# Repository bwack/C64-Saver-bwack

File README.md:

C64 Saver v1 and v2
- Overvoltage protection for the C64 and its power brick.

Designed by BWACK 2018
CERN OPEN HARDWARE LICENSE v1.2
http://www.ohwr.org/

The KiCad and other design files are available on GitHub:
https://github.com/bwack/

All text above must be included in any redistribution

# Warning: latest version of the savers are not tested.

# Bwack's C64 saver designs.

The C64 Saver 2 is an open-source project intended to make overvoltage protection available and easy to make for anyone interested in using the old Commodore power brick together with the C64. The power brick is 30-40 years old, and it is known for failure with overvoltage. This is caused sometimes because of broken solder joints on the regulator or the regulator itself failing.

## What has changed in v2 ?
- The design is modular.
- Spike protection. Handles hotswapping and switch bouncing better.
- It is much much easier and faster to make. Most people can make it!

## The base board (C64 Saver 2 SMD or Throughhole)
The base board is all you need for overvoltage protection. Through hole parts except for the mosfet, but it is large and easy to solder, no special tools needed other than your solder iron. The board shape fits the Hammond 1551g project case.
* Note: You need to bridge pin 4 and 5 in J2 and pin 4 and 5 in J4 if you are not using the base board in combination with the addon board or the relay board. The reason for this is that, with the addon board, we need to route the current through a sensing circuit. When the addon board is not used, we need to route it directly to the mosfet and terminals.

There is also a SMD version for those who like to reflow soldering.

## The addon board
The C64 saver addon board is a hat for the base board, and adds software control, instrumentation on both ac and dc side, and an optional 128x32 OLED display. The aim for this project is to make a tool for C64 repairers. The 9VAC and 5VDC are fully isolated. Software control and instrumentation is useful if you are repairing C64s. You can set the output to shut down in case of an overcurrent condition. If an overvoltage happens you can configure the saver to auto reset or keep the power from comming back on again. There are several reasons why you might want this. C64 PSUs that need service, the capacitors are dry and the 5VDC has an AC component on it. The saver would normally just go on and off at 100Hz. The software control can detect this. The other problem is if the computer has a faulty chip that cause massive current draw on the 5V. The fuse might not blow because it is not enough, then you can configure the saver cut if you desire. I'm not gonna lie. This is my pet project, and the cost has not been a topic on my mind.

The C64 Saver Addon Board 1.4:

Youtube video of me testing the addon board installed on the C64 Saver 2.

The relay and hold board is archived in the oldfiles folder.

## C64 Saver OCP

OCP, not robocop, but overcurrent protection. Is a new circuit that I'm working on. It has three LEDs and a button. The overvoltage protection circuit is the same as before. The overcurrent will light the yellow led and keep it lit and keep the output OFF after an overcurrent event.

## The old design
I have decided to release my older C64 Saver v1. The board that fits inside a connector. Time and skill is super high on this product so be warned ! (SMD 0603, solder blob connections, tight spaces and short circuit hazards).

## Gerbers
If you are looking for gerbers, click the releases tab. There you will find a zip file of gerber for each release.

# BOM
All bill of materials (BOM) are moved into the respective project folders. I have added digikey etc order no. in the parts in the schematics such that they will show up in the interactive boms.

Here are the interactive BOMs:

[ibom for C64 Saver Throughole 2.6](https://htmlpreview.github.io/?https://github.com/bwack/C64-Saver-bwack/blob/master/C64%20Saver%20Throughhole%202.6/bom/ibom.html)

[ibom for C64 Saver SMD 2.6](https://htmlpreview.github.io/?https://github.com/bwack/C64-Saver-bwack/blob/master/C64%20Saver%20SMD%202.6/bom/ibom.html)

[ibom for C64 Addon Board 1.4](https://htmlpreview.github.io/?https://github.com/bwack/C64-Saver-bwack/blob/master/addon%20board%201.4/bom/ibom.html)

[ibom for C64 Saver OCP 0.1](https://htmlpreview.github.io/?https://github.com/bwack/C64-Saver-bwack/blob/master/C64%20Saver%20OCP%200.1/bom/ibom.html)

# Changelog:

- C64 Saver 2.6 (THT+SMD) and Addon Board 1.4 (2023-04-02)
  - Replaced 7n2002 with BC547/BC847 to fix the tolerance issues.
  - Throughhole and SMD: same version numbers, same circuits, same reference numbers.
  - Red LED is switched by TL431 and Green by BC547/BC847.
  - Added LEDs to the Throughhole version. It was a challenge.
  - Fix: The Addon Board 1.3 had incorrect pinout for the 5V reg.
  - I never tested the Addon Board 1.3, but thanks to Retroisten who sent.
  me images and advicing me about he pinout, I'm very happy about it. He also
  showed me that it does work, with the regulator hacked in.  In this version 1.4
  it is working.

- C64 Saver 2.5 (SMD) (2020-09-13)
  - Added fault LED and power LED
  - 0805 SMD resistors
  - SOT23-5 TL431 and NMOS

- RelayHold 0.2 (2019-08-25)
  - Initial release
  - All through-hole parts.

- Addon Board 1.3 (2019-05-24)
  - Changed optocoupler footprint to more common SOIC-4_4.55x2.6mm_P1.27mm
  - Larger 5V regulator on 9vac side for less heat
  - replaced 100uF tantalum with 3x 47uF 1206 MLCC
  - kicad 5.1.0 project

- Addon Board 1.2 (2018-11-11)
  - Swapped HOLD_ with SENSE_VAC on the MCU. SENSE_VAC needs ADC.
  - Correct the mixed up SDA and SCL.
  - 5V supply to the 5V section is moved to VIN+ (before the shunt).
    To not pull power through the sensing resistor.
  - 4k7 I2C pullups.https://htmlpreview.github.io/?https://github.com/bwack/C64-Saver-bwack/blob/develop/C64%20Saver%20Throughhole%202.6/bom/ibom.html

- C64 Saver 2.4 (2018-09-23)
  - Support lower Vth on Q1. Resistor divider R7 and R8.
  - Remove C2 to make room for resistor divider.
  - Changed R5 to 3k3 to reduce BOM size.
  - New layout and routing.

- Addon Board 1.1 (2018-09-23)
  - ATtiny85 is a 8S2 package and two mm wider than SOIC8.
  - Read overvoltage signal on reset pin using ADC. Added voltage divider.
  - Replace MCP1700 with MCP1703. Supporting higher Vin_max

- C64 Saver 2.3 (2018-08-18)
  - Q1 2N7002 pin 1 and 2 rotated
  - Q2 Reversed drain and source
  - Increased pullup on Q1 drain.
  - Repurposed R5 as pullup for Q1 drain.
  - tested bodged v2.2 prototype, wohttps://htmlpreview.github.io/?https://github.com/bwack/C64-Saver-bwack/blob/develop/C64%20Saver%20Throughhole%202.6/bom/ibom.htmlrking!

- C64 Saver 2.2 (2018-08-16)
  - R1 was rotated.

- C64 Saver 2.1 & Addon 1.0 (2018-07-23)
  - 5x 9VAC pins. 9VAC1 current (4x) + 9VAC2.
  - Moved GND pin.
  - Changed board size to fit Hammond1551g
  - C64 Saver board:
    - Smaller throughole resistors
    - Moved C1 closer to input circuits.
  - Addon board:
    - VAC sense circuit with voltage divider.
    - 5V regulator on VCC pin. RAW pin disconnected.
    - Pullups on I2C busses.
    - SSOP-4 optocoupler packages
    - Another regulator on the 5V side to protect the iso1541 and ina219.

- C64 Saver 2.0beta & Addon 1.0beta (2018-07-02)
  - New design.
  - Protected sensitive parts.
  - baseboard: throughhole parts.
  - C64 saver 2 addon board.
  - problem: has conflicting pinouts.

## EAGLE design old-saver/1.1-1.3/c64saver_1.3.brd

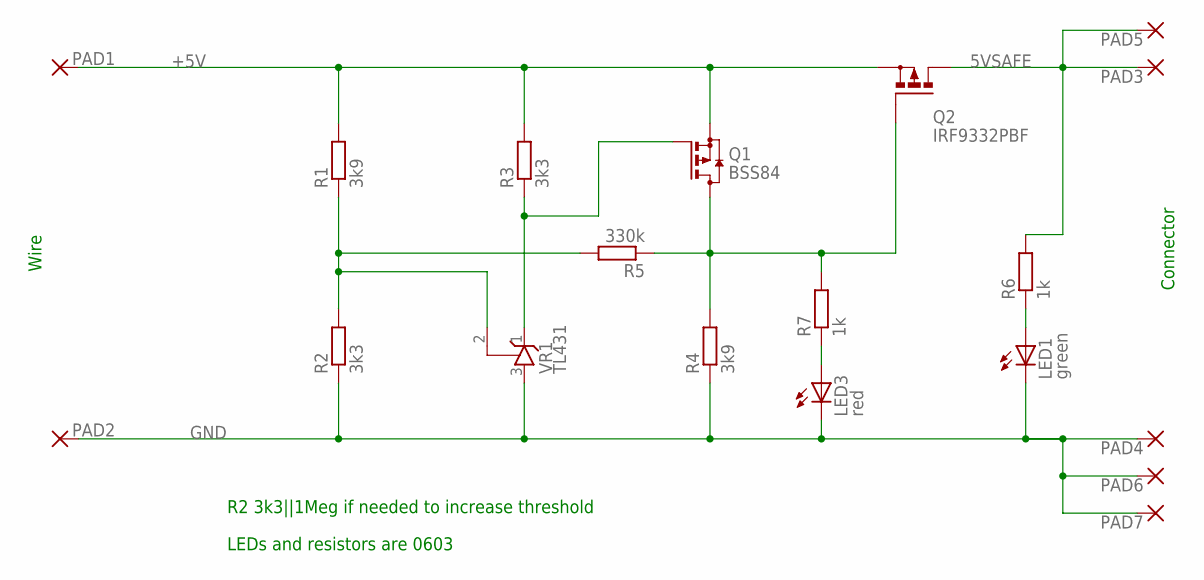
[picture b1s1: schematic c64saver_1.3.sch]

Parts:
LED1: green; CHIPLED_0603
LED3: red; CHIPLED_0603
PAD1, PAD2, PAD4, PAD6, PAD7: WIREPADSMD1,27-254; SMD1,27-2,54
PAD3, PAD5: WIREPADSMD2,54-2,54; SMD2,54-2,54
Q1: BSS84; SOT23
Q2: IRF9332PBF; SO-08
R1, R4: 3k9; R0603
R2, R3: 3k3; R0603
R5: 330k; R0603
R6, R7: 1k; R0603
VR1: TL431; SOT23

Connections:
5VSAFE: PAD3.1, PAD5.1, Q2.5 (D), Q2.6 (D), Q2.7 (D), Q2.8 (D), R6.2
+5V: PAD1.1, Q1.2 (S), Q2.1 (S), Q2.2 (S), Q2.3 (S), R1.2, R3.2
GND: LED1.C, LED3.C, PAD2.1, PAD4.1, PAD6.1, PAD7.1, R2.1, R4.1, VR1.3 (A)
unnamed: LED3.A, R7.1
unnamed: R1.1, R2.2, R5.2, VR1.2 (R)
unnamed: LED1.A, R6.1
unnamed: Q1.1 (G), R3.1, VR1.1 (C)
unnamed: Q1.3 (D), Q2.4 (G), R4.2, R5.1, R7.2

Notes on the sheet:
R2 3k3||1Meg if needed to increase threshold
Wire
Connector
LEDs and resistors are 0603

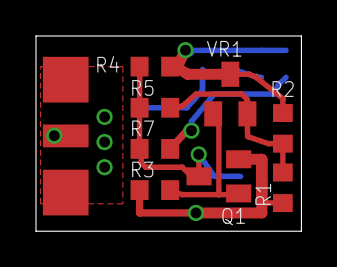
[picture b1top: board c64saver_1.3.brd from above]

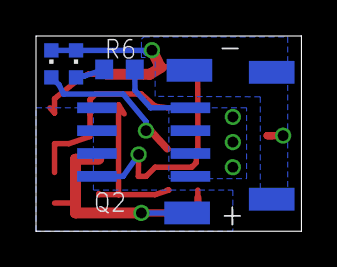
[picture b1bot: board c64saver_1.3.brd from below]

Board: 2 copper layers, 14.7 x 10.8 mm, 19 parts (8 on the bottom side), 8 nets.

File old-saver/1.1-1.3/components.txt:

The fet: IRF9333PBF (on sale)

Kontrollkabel uskjermet 4 x0.56 mm² uskjermet, UL-LIYY 4XAWG20, 2464/1061
10-416-96 19.90 pr meter

1   1k           R-EU_R0603         R7                                      
2   3k3          R-EU_R0603         R2, R3                                  
2   3k9          R-EU_R0603         R1, R4                                  
1   100k         R-EU_R0603         R5                                      
1   BSS84        BSS84              Q1                                      
1   IRF9332PBF   P-MOSFET-SO8       Q2                                      
1   RED_SIDEView LEDCHIPLED_1206    LED1                                    
1   TL431        TL431CLPSOT23      VR1

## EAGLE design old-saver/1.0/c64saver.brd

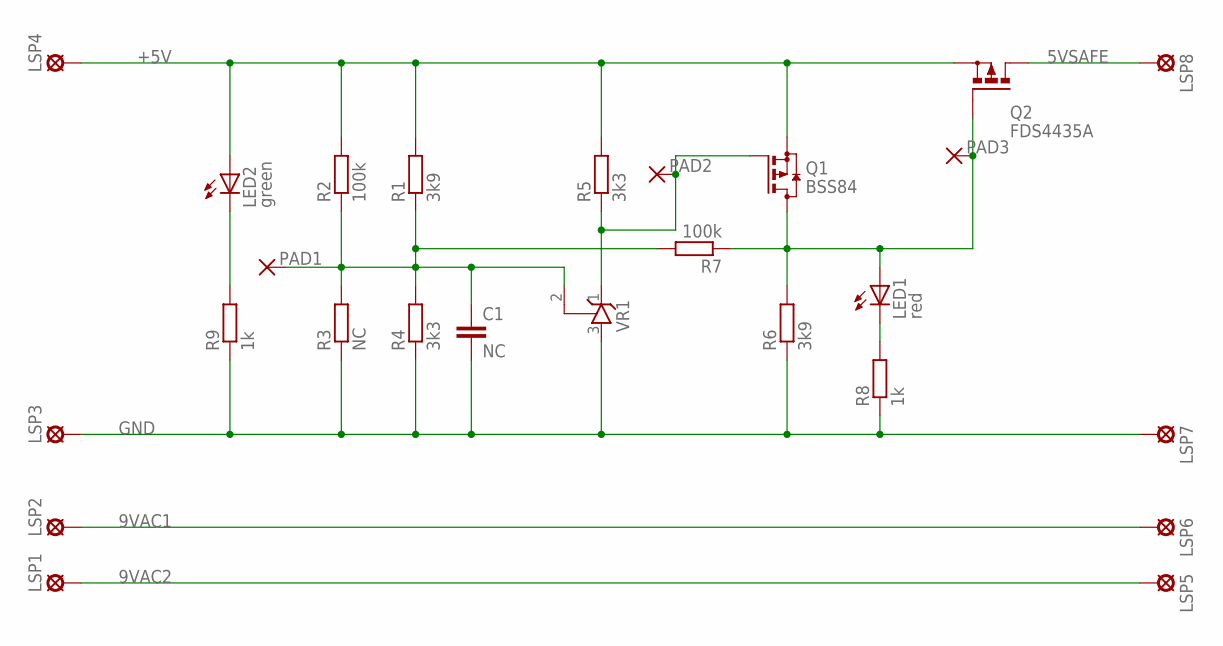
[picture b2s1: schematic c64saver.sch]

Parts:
C1: NC; C0603
LED1: red; CHIPLED_1206
LED2: green; CHIPLED_1206
LSP1, LSP2, LSP3, LSP4, LSP5, LSP6, LSP7, LSP8: SE14
PAD1, PAD2, PAD3: SMD2; SMD1,27-2,54
Q1: BSS84; SOT23
Q2: FDS4435A; SO-08
R1, R6: 3k9; R0603
R2, R7: 100k; R0603
R3: NC; R0603
R4, R5: 3k3; R0603
R8, R9: 1k; R0603
VR1: TL431CLPSOT23; SOT23

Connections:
5VSAFE: LSP8.MP, Q2.5 (D), Q2.6 (D), Q2.7 (D), Q2.8 (D)
9VAC1: LSP2.MP, LSP6.MP
9VAC2: LSP1.MP, LSP5.MP
+5V: LED2.A, LSP4.MP, Q1.2 (S), Q2.1 (S), Q2.2 (S), Q2.3 (S), R1.2, R2.2, R5.2
GND: C1.2, LSP3.MP, LSP7.MP, R3.1, R4.1, R6.1, R8.1, R9.1, VR1.3 (A)
unnamed: C1.1, PAD1.1, R1.1, R2.1, R3.2, R4.2, R7.2, VR1.2 (R)
unnamed: LED1.C, R8.2
unnamed: LED2.C, R9.2
unnamed: PAD2.1, Q1.1 (G), R5.1, VR1.1 (C)
unnamed: LED1.A, PAD3.1, Q1.3 (D), Q2.4 (G), R6.2, R7.1

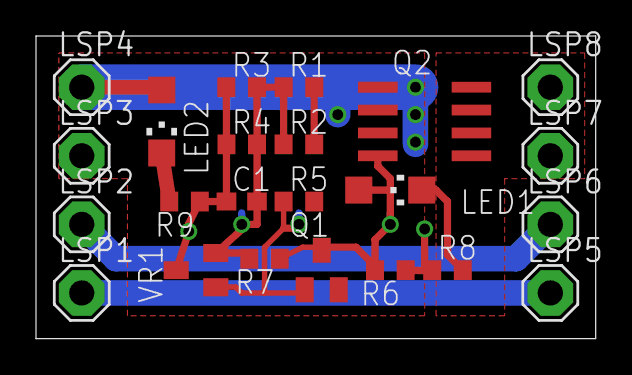
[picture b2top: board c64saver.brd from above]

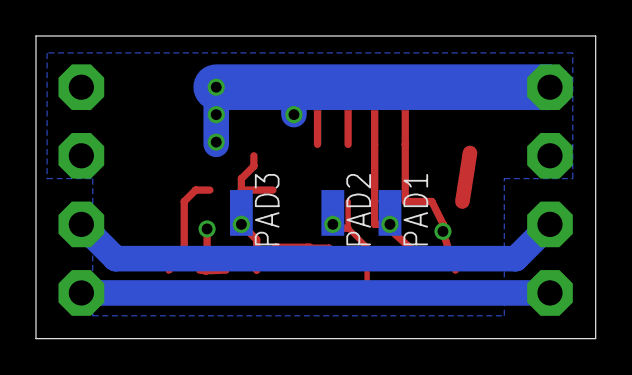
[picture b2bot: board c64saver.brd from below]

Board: 2 copper layers, 31.1 x 16.8 mm, 26 parts (3 on the bottom side), 10 nets.

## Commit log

2018-06-13 inital commit 1.0 saver
2018-06-13 1.1 to 1.3
2018-06-17 C64 Saver 2 first commit
2018-06-17 Tidy up project libraries. Relative paths
2018-06-22 layed out and routed
2018-06-22 schematic pdf and image of pcb
2018-06-24 readme
2018-06-25 LICENSE, Changelog
2018-06-25 Name, revision, author on silk.s
2018-06-25 revision on addon board
2018-06-25 deleted backup file
2018-06-25 deleted .bak file
2018-07-02 dimensions
2018-07-02 saver 2.0beta - addon 1.0beta
2018-07-02 added gnd, 5x 9vac pins, moved c1 closer to input circuit
2018-07-03 eddited schematic of addon board
2018-07-04 SOP4 model
2018-07-05 ssop. 0603 capacitors
2018-07-05 another regulator on 5v to protect the ina219 and iso1541
2018-07-08 fit to hammond1591, larger board.
2018-07-08 hammond1551G. It will be a tight fit !
2018-07-10 addon board component placement done. layout begun.
2018-07-11 more routing. mostly power nets remaining
2018-07-12 routing completed
2018-07-12 included 2.0beta (throughhole) and 2.1 smd is the upcomming version
2018-07-22 Release 2.1 and addon 1.0
2018-08-08 Editting V2.2. R1 was rotated. why.
2018-08-08 Remove gerbers from sources. See Releases for gerbers.
2018-08-08 Ignore gerber
2018-08-09 resistor values
2018-08-09 date and version
2018-08-16 release saver v2.2
    got fix for rotated resistor
2018-08-16 merge
2018-08-18 v2.3
2018-09-02 working makefile and helloworld example
2018-09-08 Change: ATtiny footprint, ADC used with reset input
2018-09-08 Added Adam Honse's USI I2C Slave Master library for ATTiny
2018-09-09 Board rerouted
2018-09-09 modified usi_i2c_master to support attiny85
2018-09-16 The i2c in i2c_master and sd1306 source code does not go well together
    might want to rewrite the code for the sd1306 and use the usi_i2c_master library. Might be slower though.
2018-09-16 c64 saver 2 bom with elfa order numbers
2018-09-16 BOM for the addon board
2018-09-16 bom addon board
2018-09-16 female male
2018-09-23 New layout new routing. Resistor divider to support low Vth. #13
2018-09-23 I suppose saving the design helps #13
2018-09-23 Addon board ready for new release #9
2018-09-23 type
2018-09-24 WTF, text on titleblock on copper layer???
2018-10-02 testing the 8x16 font and num2str.c
2018-10-09 Rotated 3D drawing of D1 on addon board
    Rotated only the 3D drawing of D1. The layout is the same.
2018-10-19 troubleshooting INA I2C
2018-10-19 cleanup
2018-10-20 removed usi_i2c_master added INA I2C INA I2C works now but MCU still hangs if OLED I2C is used too
2018-10-20 removed usi_i2c_master
2018-10-20 INA I2C works as standalone but MCU freezes when INA I2C is used with ssd1306 I2C
2018-10-21 actually, INA219 is not responding on any port
2018-10-21 fixed CPU clock improved I2C timings
2018-10-21 improved ACK/NAK timing
2018-10-21 further I2C timing improvements
2018-10-22 repeatedly detecting INA219 in infinite loop
2018-10-23 more i2c timing improvements
2018-11-01 still troubleshooting INA I2C
2018-11-01 added stop condition on startup to prevent i2c garbage interference
2018-11-03 still troubleshooting and still no life signs from INA
2018-11-04 addonboard: 5V moved to VIN+, and fixed SDA2 and SCL2. #16 #17
2018-11-04 work in progress
2018-11-04 troubleshooting SDA always high bug
2018-11-08 4k7 pullups + readme
2018-11-08 old code
2018-11-11 Swapped HOLD_ with SENSE_VAC #18
2018-11-30 main loop timing, button logic, AC adc. Worked out warnings (-Werror).
2018-12-02 Firmware: New features
2018-12-02 Firmware: Settings on EEPROM.
2019-01-05 release firmware 1.0
2019-05-19 bom update
2019-05-20 MLCC 1210 cap and optoisolators changed to Package_SO:SOIC-4_4.55x2.6mm_P1.27mm
    Not finished routing. Needs more of the 1210 caps.
2019-05-23 Addon Board 1.3 (2019-05-24)
    - Changed optocoupler footprint to more common SOIC-4_4.55x2.6mm_P1.27mm
    - Larger 5V regulator on 9vac side for less heat
    - replaced 100uF tantalum with 3x 47uF 1206 MLCC
    - kicad 5.1.0 project
2019-05-23 screenshot of the board
2019-05-24 year and version on silkscreen
    switched to kicad 5.1.0 -> 5.1.2
2019-06-23 kicad 5.1.0 -> 5.1.2
2019-07-16 Delete C64Saver2-addon-BOM.txt
    Double documentation !
2019-07-16 Revert "Delete C64Saver2-addon-BOM.txt"
    This reverts commit ba7545e9be7d77e44fc48137fce718ff76d0ae6d.
2019-08-25 Relay Hold Addon Board 0.2
2020-02-13 Updated readme with BOM
2020-08-29 Updated bom is in the readme. This bom file was outdated. Deleteing it.
2020-08-29 Added IN/OUT to bottom silkscreen. upped project to Kicad 5.1.2
2020-09-12 C64 Saver 2.5 ready for prototype
2020-09-12 the drill file
2020-09-13 Added old v2.4 files in C64 Saver 2.4 folder
2020-09-27 pdf update
2020-09-27 test
2020-09-27 sometest
2022-02-08 added 3D images and fixed readme #27
2023-03-20 THT 2.6 update. renamed some folders to separate SMD and THT versions.
2023-03-20 some deleted folders
2023-03-20 removed the c64 saver tester project.
2023-03-21 SMD version 2.6 layout and schematics. Both THT and SMD are now on same version. should have same references.
2023-03-22 layout for tht 2.6. added connector for leds as alternative to smd leds
2023-03-25 Updated Throughole version (2.6). Gerbers, BOM, PDF etc. Moved old versions to folders. Might remove later
2023-04-01 Preparing for Saver 2.6, moving 2.5 and 2.4 to oldfiles folder
2023-04-02 finished OCP version ready for testing
2023-04-02 added digi-key order numbers to ibom
2023-04-02 Added ibom for addon board, and put the elfa+RS components into the parts/ibom
2023-04-02 updated schematics pdfs
2023-10-18 Redesign with improvements: - LED2 pulling from 5V_SAFE to avoid higher V on pin1 of Q1. This had an effect of reduce the on saturation of Q2 and limiting overall current slightly. Also this allows a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
2023-10-20 Renamed folder to remove version number and moved easyeda to own folder in prep for kicad version. No code changes.
2023-10-20 Adding 2.6 to folder (so the difference is visible in a PR)
2023-10-20 2.7 with iBom and gerbers
2023-11-19 Updates to both kicad and easyeda versions. I found a missing connection in the earlier untested Kicad version. :(
2023-11-19 Missed the easyeda main files.
2023-11-19 Strictly moved folders, no changes to files, to better mirror Bwack's original format of folders.
2023-11-19 Version 2.7 of the through hole version, squashed merge for cleanliness.
